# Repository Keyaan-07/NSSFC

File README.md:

# NSSFC

NSSFC is an FPV flight controller made with the STM32F405 and it has an IMU, Barometric pressure sensor and a magnetometer. It uses the betaflight as firmware(thus no firmware directory in this repository). The package is a typical 37mmx37mm.  

View the board on [KiCanvas](https://kicanvas.org/?repo=https%3A%2F%2Fgithub.com%2FKeyaan-07%2FNSSFC%2Ftree%2Fmain%2Fhardware)  

We made it to learn more about Flight controllers and make PCBs in a small area, especially something like 37x37mm!  

<!--  -->

## How to assemble:  
1. Order PCBs and components from the [/hardware/production](/hardware/production/) folder and order them from your supplier and PCB fab. Don't forget to get a stencil along with your PCB!
2. Place the PCB on a flat surface and place the stencil over it. 
3. Use medium-temp solder paste to put the soldermask pattern over the PCB. 
4. Carefully place all the components, use the [ibom](/hardware/bom/ibom.html) for smooth placement. 
5. Solder it in a reflow-oven or a hotplate!
6. You're done!!

## Firmware Flashing Guide:  
1. Hold the BOOT0 button and put in the USB into your computer.  
2. We will use [betaflight web configurator](https://app.betaflight.com/) to flash the lastest build. [here](https://github.com/betaflight/betaflight/releases/download/2026.6.2/betaflight_2026.6.2_STM32F405.hex) is the latest build, download it!  
3. Also, download the config file from the [/config](/config/) folder. 
3. Go to the firmware flasher tab in the betaflight app.  
4. Click load local firmware, then select the downloaded `nssfc.config` file.  
5. Click Load local firmware again, and then select the `.hex` file you downloaded.  
6. Click Flash firmware to flash the firmware.  
7. After the firmware has been flashed, go to the home page and then click connect, to connect to the FC.  
8. A prompt asking _Apply custom defaults_ should pop up, click yes. 
9. Your flashing part is done! Happy Flying!

[here](https://betaflight.com/docs/wiki/guides/archive/Unified-Targets) is the source for the above steps. 

# BOM
|Designator                                                |Function        |Value           |Footprint                               |Quantity|Price        |Amount |Link                                              |
|----------------------------------------------------------|----------------|----------------|----------------------------------------|--------|-------------|-------|--------------------------------------------------|
|PCB                                                       |                |                |                                        |5       |             |2      |https://jlcpcb.com/                               |
|Stencil                                                   |                |                |                                        |1       |             |3.1    |https://jlcpcb.com/                               |
|C1, C16, C2                                               |Capacitor       |2.2u            |402                                     |3       |0.0054       |0.0162 |https://www.lcsc.com/product-detail/C12530.html   |
|C10                                                       |Capacitor       |1u              |402                                     |1       |0.047        |0.047  |https://www.lcsc.com/product-detail/C1518208.html |
|C11                                                       |Capacitor       |4.7u            |402                                     |1       |0.0275       |0.0275 |https://www.lcsc.com/product-detail/C20624278.html|
|C12, C13, C14, C15, C17, C19, C23, C25, C5, C6, C7, C8, C9|Capacitor       |100n            |402                                     |13      |0.0045       |0.0585 |https://www.lcsc.com/product-detail/C5182432.html |
|C20                                                       |Capacitor       |22u             |805                                     |1       |0.17         |0.17   |https://www.lcsc.com/product-detail/C602037.html  |
|C21, C22, C24                                             |Capacitor       |10u             |805                                     |3       |0.18         |0.54   |https://www.lcsc.com/product-detail/C2932476.html |
|C3, C4                                                    |Capacitor       |15p             |402                                     |2       |0.025        |0.05   |https://www.lcsc.com/product-detail/C441742.html  |
|D1, D2                                                    |Diode           |D_Schottky      |D_SOD-123F                              |2       |0.035        |0.07   |https://www.lcsc.com/product-detail/C432153.html  |
|D3, D4, D5                                                |LED             |LED             |402                                     |3       |0.054        |0.162  |https://www.lcsc.com/product-detail/C2980183.html |
|J1                                                        |USB C receptacle|USB_C_Receptacle|USB_C_Receptacle_XKB_U262-16XN-4BVC11   |1       |0.059        |0.059  |https://www.lcsc.com/product-detail/C393939.html  |
|L1                                                        |Inductor        |4.7u            |L_Changjiang_FNR4020S                   |1       |0.082        |0.082  |https://www.lcsc.com/product-detail/C167828.html  |
|R1, R6                                                    |Resistor        |10k             |402                                     |2       |0.0425       |0.085  |https://www.lcsc.com/product-detail/C3020235.html |
|R2, R3                                                    |Resistor        |4.7k            |402                                     |2       |0.0026       |0.0052 |https://www.lcsc.com/product-detail/C25900.html   |
|R4, R5                                                    |Resistor        |5.1k            |402                                     |2       |0.006        |0.012  |https://www.lcsc.com/product-detail/C278598.html  |
|R7                                                        |Resistor        |1k              |402                                     |1       |0.066        |0.066  |https://www.lcsc.com/product-detail/C427241.html  |
|R8                                                        |Resistor        |220             |402                                     |1       |0.002        |0.002  |https://www.lcsc.com/product-detail/C2909336.html |
|R9                                                        |Resistor        |100             |402                                     |1       |0.026        |0.026  |https://www.lcsc.com/product-detail/C427204.html  |
|SW1                                                       |Push button     |SW_Push         |SW_SPST_PTS810                          |1       |0.3425       |0.3425 |https://www.lcsc.com/product-detail/C221895.html  |
|U1                                                        |MCU             |STM32F405RGTx   |LQFP-64_10x10mm_P0.5mm                  |1       |6.01         |6.01   |https://www.lcsc.com/product-detail/C15742.html   |
|U2                                                        |Flash           |W25Q128JVP      |WSON-8-1EP_6x5mm_P1.27mm_EP3.4x4.3mm    |1       |2.82         |2.82   |https://www.lcsc.com/product-detail/C2441427.html |
|U3                                                        |magnetometer    |QMC5883P        |LGA-16_3x3_Pitch0.5mm_QMC5883P          |1       |1.57         |1.57   |https://www.lcsc.com/product-detail/C2847467.html |
|U4                                                        |IMU             |ICM-20602       |LGA-16_3x3mm_P0.5mm_LayoutBorder3x5y    |1       |6.02         |6.02   |https://www.lcsc.com/product-detail/C97633.html   |
|U5                                                        |Pressure Sensor |BMP580          |ST_HLGA-10_2x2mm_P0.5mm_LayoutBorder3x2y|1       |1.21         |1.21   |https://www.lcsc.com/product-detail/C22391138.html|
|U6                                                        |Buck            |AP63205WU       |TSOT-23-6                               |1       |0.43         |0.43   |https://www.lcsc.com/product-detail/C2071056.html |
|U7                                                        |LDO             |TLV75733PDBV    |SOT-23-5                                |1       |0.2          |0.2    |https://www.lcsc.com/product-detail/C485517.html  |
|Y1                                                        |Crystals        |25MHz           |Crystal_SMD_3225-4Pin_3.2x2.5mm         |1       |0.1          |0.1    |https://www.lcsc.com/product-detail/C70582.html   |
|                                                          |                |                |                                        |        |LCSC shipping|9.3    |                                                  |
|                                                          |                |                |                                        |        |PCB Shipping |11.25  |                                                  |
|                                                          |                |                |                                        |        |Total        |45.8309|                                                  |

Made by Keyaan and Ahad

# Licensing
Licensed under the MIT License!

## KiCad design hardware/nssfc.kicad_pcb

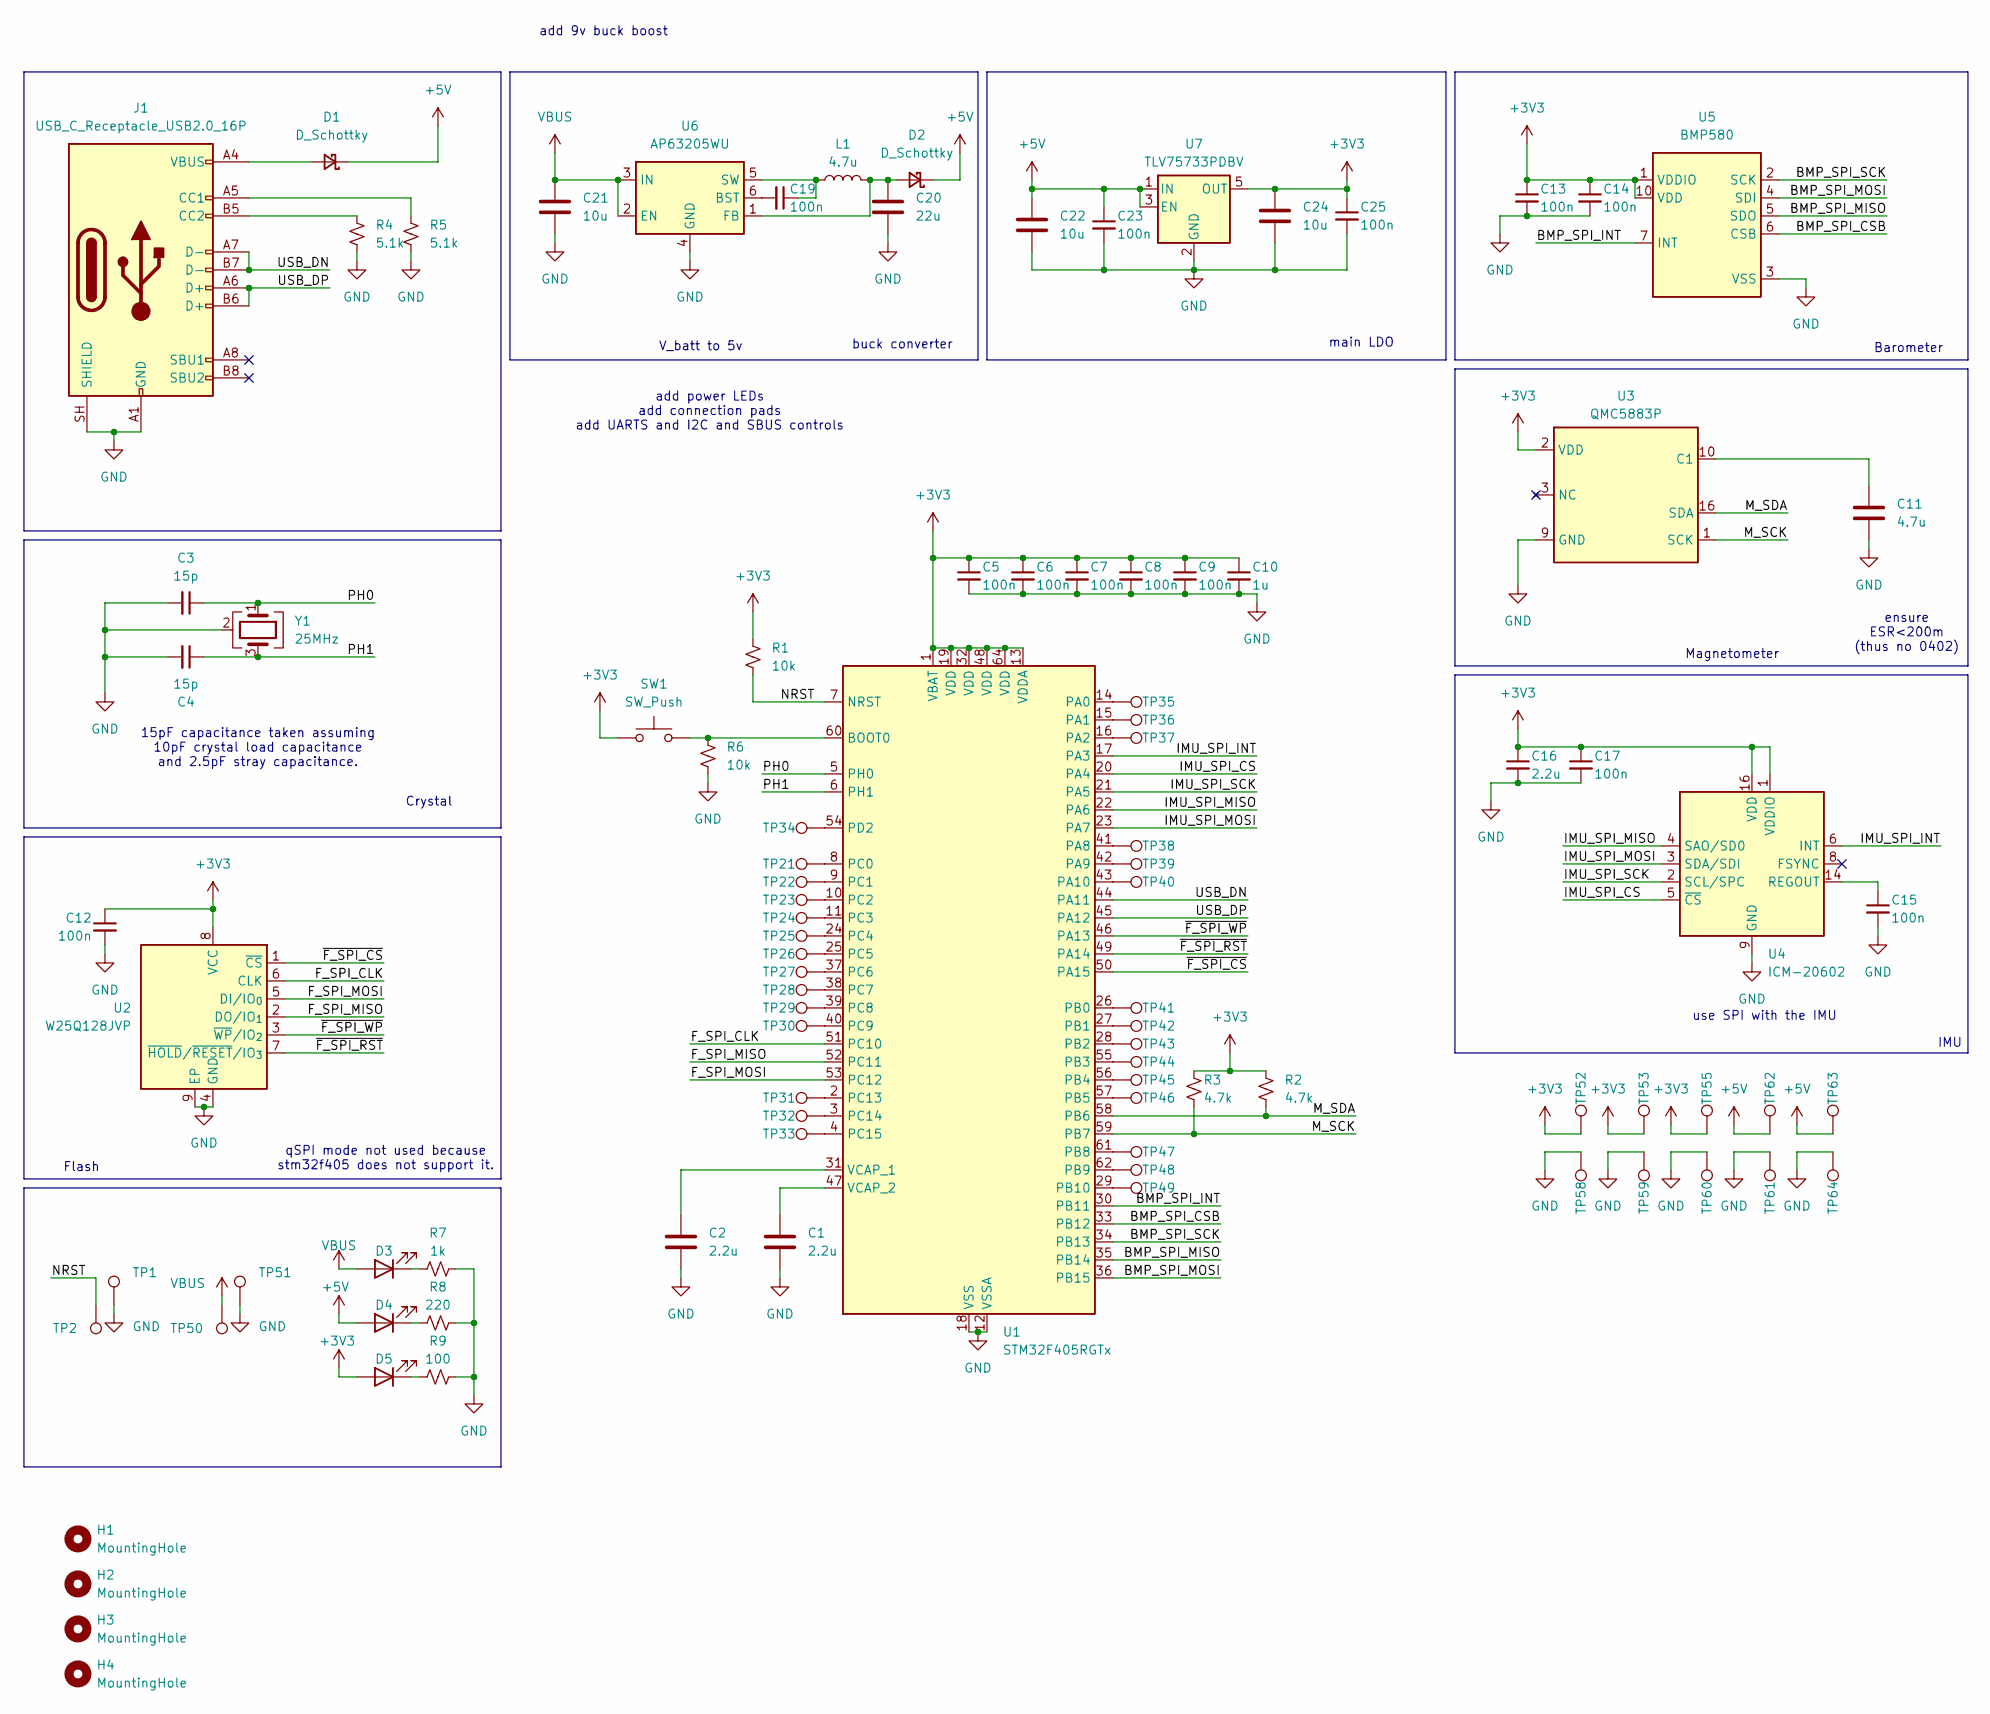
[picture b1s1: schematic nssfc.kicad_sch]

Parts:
C1, C2, C16: 2.2u; C_0402_1005Metric
C3, C4: 15p; C_0402_1005Metric
C5, C6, C7, C8, C9, C12, C13, C14, C15, C17, C19, C23, C25: 100n; C_0402_1005Metric
C10: 1u; C_0402_1005Metric
C11: 4.7u; C_0805_2012Metric
C20: 22u; C_0805_2012Metric
C21, C22, C24: 10u; C_0805_2012Metric
D1, D2: D_Schottky; D_SOD-123F
D3, D4, D5: LED; LED_0402_1005Metric
H1, H2, H3, H4: MountingHole; MountingHole_3.2mm_M3
J1: USB_C_Receptacle_USB2.0_16P; USB_C_Receptacle_XKB_U262-16XN-4BVC11
L1: 4.7u; L_Changjiang_FNR4020S
R1, R6: 10k; R_0402_1005Metric
R2, R3: 4.7k; R_0402_1005Metric
R4, R5: 5.1k; R_0402_1005Metric
R7: 1k; R_0402_1005Metric
R8: 220; R_0402_1005Metric
R9: 100; R_0402_1005Metric
SW1: SW_Push; SW_SPST_PTS810
TP1, TP2: TestPoint; TestPoint_Pad_1.0x1.0mm
TP21, TP22, TP23, TP24, TP25, TP26, TP27, TP28, TP29, TP30, TP31, TP32, TP33, TP34, TP35, TP36, TP37, TP38, TP39, TP40, TP41, TP42, TP43, TP44, TP45, TP46, TP47, TP48, TP49, TP52, TP53, TP55, TP58, TP59, TP60, TP61, TP62, TP63, TP64: TestPoint; PAD_1.5mm
TP50, TP51: TestPoint; TestPoint_Pad_2.0x2.0mm
U1: STM32F405RGTx; LQFP-64_10x10mm_P0.5mm
U2: W25Q128JVP; WSON-8-1EP_6x5mm_P1.27mm_EP3.4x4.3mm
U3: QMC5883P; LGA-16_3x3_Pitch0.5mm_QMC5883P
U4: ICM-20602; LGA-16_3x3mm_P0.5mm_LayoutBorder3x5y
U5: BMP580; ST_HLGA-10_2x2mm_P0.5mm_LayoutBorder3x2y
U6: AP63205WU; TSOT-23-6
U7: TLV75733PDBV; SOT-23-5
Y1: 25MHz; Crystal_SMD_3225-4Pin_3.2x2.5mm

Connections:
+3V3: C5.1, C6.1, C7.1, C8.1, C9.1, C10.1, C12.1, C13.1, C14.1, C16.1, C17.1, C24.1, C25.1, D5.2 (A), R1.1, R2.1, R3.1, SW1.1, TP52.1 (1_1), TP53.1 (1_1), TP55.1 (1_1), U1.1 (VBAT), U1.13 (VDDA), U1.19 (VDD), U1.32 (VDD), U1.48 (VDD), U1.64 (VDD), U2.8 (VCC), U3.2 (VDD), U4.1 (VDDIO), U4.16 (VDD), U5.1 (VDDIO), U5.10 (VDD), U7.5 (OUT)
+5V: C22.1, C23.1, D1.1 (K), D2.1 (K), D4.2 (A), TP62.1 (1_1), TP63.1 (1_1), U7.1 (IN), U7.3 (EN)
/BMP_SPI_CSB: U1.33 (PB12), U5.6 (CSB)
/BMP_SPI_INT: U1.30 (PB11), U5.7 (INT)
/BMP_SPI_MISO: U1.35 (PB14), U5.5 (SDO)
/BMP_SPI_MOSI: U1.36 (PB15), U5.4 (SDI)
/BMP_SPI_SCK: U1.34 (PB13), U5.2 (SCK)
/F_SPI_CLK: U1.51 (PC10), U2.6 (CLK)
/F_SPI_MISO: U1.52 (PC11), U2.2 (DO/IO_{1})
/F_SPI_MOSI: U1.53 (PC12), U2.5 (DI/IO_{0})
/IMU_SPI_CS: U1.20 (PA4), U4.5 (~CS)
/IMU_SPI_INT: U1.17 (PA3), U4.6 (INT)
/IMU_SPI_MISO: U1.22 (PA6), U4.4 (SAO/SD0)
/IMU_SPI_MOSI: U1.23 (PA7), U4.3 (SDA/SDI)
/IMU_SPI_SCK: U1.21 (PA5), U4.2 (SCL/SPC)
/M_SCK: R3.2, U1.59 (PB7), U3.1 (SCK)
/M_SDA: R2.2, U1.58 (PB6), U3.16 (SDA)
/NRST: R1.2, TP2.1 (1_1), U1.7 (NRST)
/PH0: C3.1, U1.5 (PH0), Y1.1
/PH1: C4.1, U1.6 (PH1), Y1.3
/USB_DN: J1.A7 (D-), J1.B7 (D-), U1.44 (PA11)
/USB_DP: J1.A6 (D+), J1.B6 (D+), U1.45 (PA12)
/~F_SPI_CS: U1.50 (PA15), U2.1 (~CS)
/~F_SPI_RST: U1.49 (PA14), U2.7 (~HOLD/~RESET/IO_{3})
/~F_SPI_WP: U1.46 (PA13), U2.3 (~WP/IO_{2})
GND: C1.2, C2.2, C3.2, C4.2, C5.2, C6.2, C7.2, C8.2, C9.2, C10.2, C11.2, C12.2, C13.2, C14.2, C15.2, C16.2, C17.2, C20.2, C21.2, C22.2, C23.2, C24.2, C25.2, J1.A1 (GND), J1.A12 (GND), J1.B1 (GND), J1.B12 (GND), J1.SH (SHIELD), R4.2, R5.2, R6.2, R7.2, R8.2, R9.2, TP1.1 (1_1), TP51.1 (1_1), TP58.1 (1_1), TP59.1 (1_1), TP60.1 (1_1), TP61.1 (1_1), TP64.1 (1_1), U1.12 (VSSA), U1.18 (VSS), U1.63 (VSS), U2.4 (GND), U2.9 (EP), U3.9 (GND), U3.11 (GND), U4.9 (GND), U4.10 (GND), U4.11 (GND), U4.12 (GND), U4.13 (GND), U4.15 (GND), U5.3 (VSS), U5.8 (VSS), U5.9 (VSS), U6.4 (GND), U7.2 (GND), Y1.2 (G), Y1.4 (G)
unnamed: D1.2 (A), J1.A4 (VBUS), J1.A9 (VBUS), J1.B4 (VBUS), J1.B9 (VBUS)
unnamed: C20.1, D2.2 (A), L1.2, U6.1 (FB)
unnamed: D3.1 (K), R7.1
unnamed: D4.1 (K), R8.1
unnamed: D5.1 (K), R9.1
unnamed: J1.A5 (CC1), R5.1
unnamed: J1.B5 (CC2), R4.1
unnamed: R6.1, SW1.2, U1.60 (BOOT0)
unnamed: TP35.1 (1_1), U1.14 (PA0)
unnamed: TP36.1 (1_1), U1.15 (PA1)
unnamed: TP37.1 (1_1), U1.16 (PA2)
unnamed: TP38.1 (1_1), U1.41 (PA8)
unnamed: TP39.1 (1_1), U1.42 (PA9)
unnamed: TP40.1 (1_1), U1.43 (PA10)
unnamed: TP41.1 (1_1), U1.26 (PB0)
unnamed: TP42.1 (1_1), U1.27 (PB1)
unnamed: TP43.1 (1_1), U1.28 (PB2)
unnamed: TP44.1 (1_1), U1.55 (PB3)
unnamed: TP45.1 (1_1), U1.56 (PB4)
unnamed: TP46.1 (1_1), U1.57 (PB5)
unnamed: TP47.1 (1_1), U1.61 (PB8)
unnamed: TP48.1 (1_1), U1.62 (PB9)
unnamed: TP49.1 (1_1), U1.29 (PB10)
unnamed: TP21.1 (1_1), U1.8 (PC0)
unnamed: TP22.1 (1_1), U1.9 (PC1)
unnamed: TP23.1 (1_1), U1.10 (PC2)
unnamed: TP24.1 (1_1), U1.11 (PC3)
unnamed: TP25.1 (1_1), U1.24 (PC4)
unnamed: TP26.1 (1_1), U1.25 (PC5)
unnamed: TP27.1 (1_1), U1.37 (PC6)
unnamed: TP28.1 (1_1), U1.38 (PC7)
unnamed: TP29.1 (1_1), U1.39 (PC8)
unnamed: TP30.1 (1_1), U1.40 (PC9)
unnamed: TP31.1 (1_1), U1.2 (PC13)
unnamed: TP32.1 (1_1), U1.3 (PC14)
unnamed: TP33.1 (1_1), U1.4 (PC15)
unnamed: TP34.1 (1_1), U1.54 (PD2)
unnamed: C2.1, U1.31 (VCAP_1)
unnamed: C1.1, U1.47 (VCAP_2)
unnamed: C11.1, U3.10 (C1)
unnamed: C15.1, U4.14 (REGOUT)
unnamed: C19.2, U6.6 (BST)
unnamed: C19.1, L1.1, U6.5 (SW)
VBUS: C21.1, D3.2 (A), TP50.1 (1_1), U6.2 (EN), U6.3 (IN)

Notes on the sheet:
add power LEDs add connection pads add UARTS and I2C and SBUS controls
main LDO
Flash
qSPI mode not used because stm32f405 does not support it.
15pF capacitance taken assuming 10pF crystal load capacitance and 2.5pF stray capacitance.
add 9v buck boost
ensure ESR<200m (thus no 0402)
IMU
Crystal
V_batt to 5v
buck converter
Barometer
Magnetometer
use SPI with the IMU

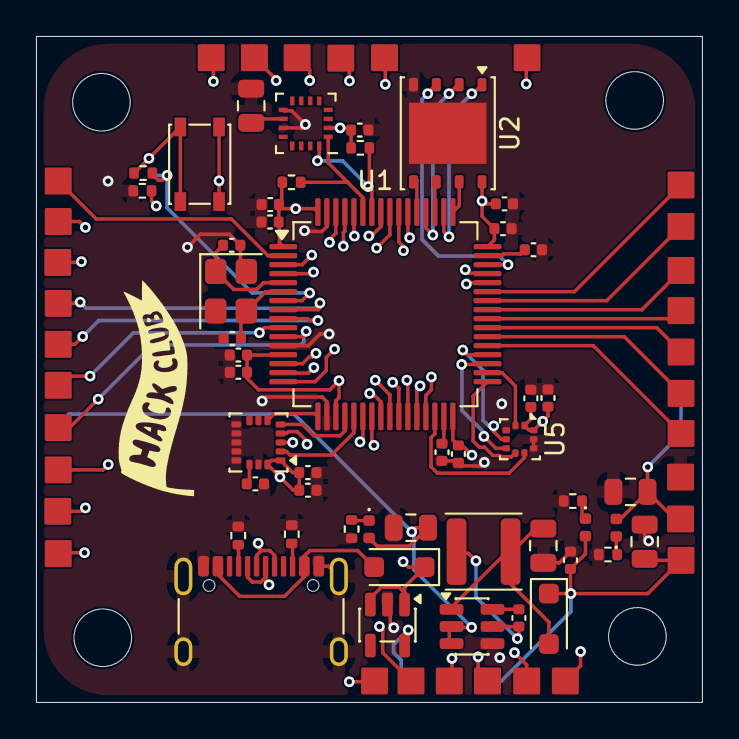
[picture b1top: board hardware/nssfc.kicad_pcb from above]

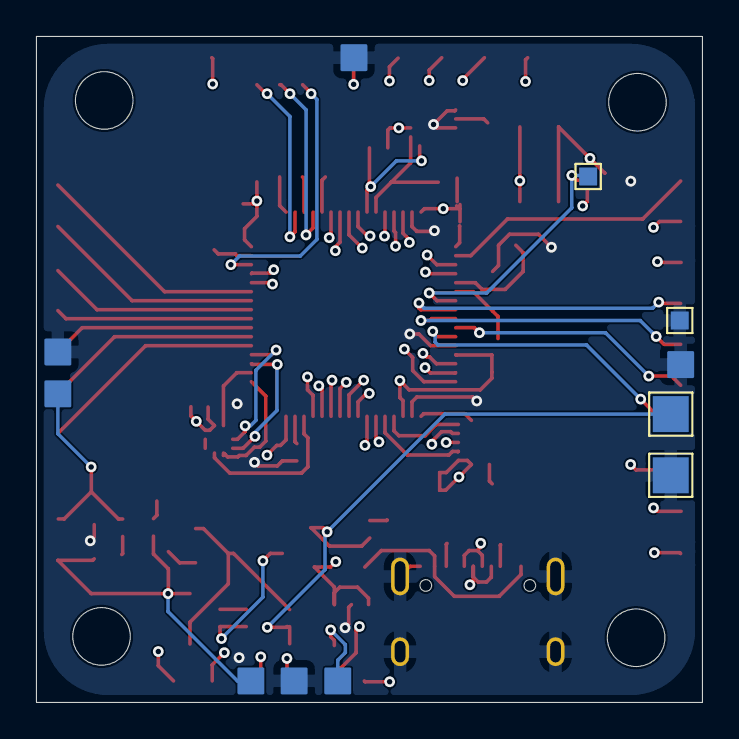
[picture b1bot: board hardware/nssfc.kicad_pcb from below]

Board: 4 copper layers, 37.0 x 37.0 mm, 96 parts (11 on the bottom side), 70 nets.

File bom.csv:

Designator,Function,Value,Footprint,Quantity,Price,Amount,Link
PCB,,,,5,,2,https://jlcpcb.com/
Stencil,,,,1,,3.1,https://jlcpcb.com/
"C1, C16, C2",Capacitor,2.2u,402,3,0.0054,0.0162,https://www.lcsc.com/product-detail/C12530.html
C10,Capacitor,1u,402,1,0.047,0.047,https://www.lcsc.com/product-detail/C1518208.html
C11,Capacitor,4.7u,402,1,0.0275,0.0275,https://www.lcsc.com/product-detail/C20624278.html
"C12, C13, C14, C15, C17, C19, C23, C25, C5, C6, C7, C8, C9",Capacitor,100n,402,13,0.0045,0.0585,https://www.lcsc.com/product-detail/C5182432.html
C20,Capacitor,22u,805,1,0.17,0.17,https://www.lcsc.com/product-detail/C602037.html
"C21, C22, C24",Capacitor,10u,805,3,0.18,0.54,https://www.lcsc.com/product-detail/C2932476.html
"C3, C4",Capacitor,15p,402,2,0.025,0.05,https://www.lcsc.com/product-detail/C441742.html
"D1, D2",Diode,D_Schottky,D_SOD-123F,2,0.035,0.07,https://www.lcsc.com/product-detail/C432153.html
"D3, D4, D5",LED,LED,402,3,0.054,0.162,https://www.lcsc.com/product-detail/C2980183.html
J1,USB C receptacle,USB_C_Receptacle,USB_C_Receptacle_XKB_U262-16XN-4BVC11,1,0.059,0.059,https://www.lcsc.com/product-detail/C393939.html
L1,Inductor,4.7u,L_Changjiang_FNR4020S,1,0.082,0.082,https://www.lcsc.com/product-detail/C167828.html
"R1, R6",Resistor,10k,402,2,0.0425,0.085,https://www.lcsc.com/product-detail/C3020235.html
"R2, R3",Resistor,4.7k,402,2,0.0026,0.0052,https://www.lcsc.com/product-detail/C25900.html
"R4, R5",Resistor,5.1k,402,2,0.006,0.012,https://www.lcsc.com/product-detail/C278598.html
R7,Resistor,1k,402,1,0.066,0.066,https://www.lcsc.com/product-detail/C427241.html
R8,Resistor,220,402,1,0.002,0.002,https://www.lcsc.com/product-detail/C2909336.html
R9,Resistor,100,402,1,0.026,0.026,https://www.lcsc.com/product-detail/C427204.html
SW1,Push button,SW_Push,SW_SPST_PTS810,1,0.3425,0.3425,https://www.lcsc.com/product-detail/C221895.html
U1,MCU,STM32F405RGTx,LQFP-64_10x10mm_P0.5mm,1,6.01,6.01,https://www.lcsc.com/product-detail/C15742.html
U2,Flash,W25Q128JVP,WSON-8-1EP_6x5mm_P1.27mm_EP3.4x4.3mm,1,2.82,2.82,https://www.lcsc.com/product-detail/C2441427.html
U3,magnetometer,QMC5883P,LGA-16_3x3_Pitch0.5mm_QMC5883P,1,1.57,1.57,https://www.lcsc.com/product-detail/C2847467.html
U4,IMU,ICM-20602,LGA-16_3x3mm_P0.5mm_LayoutBorder3x5y,1,6.02,6.02,https://www.lcsc.com/product-detail/C97633.html
U5,Pressure Sensor,BMP580,ST_HLGA-10_2x2mm_P0.5mm_LayoutBorder3x2y,1,1.21,1.21,https://www.lcsc.com/product-detail/C22391138.html
U6,Buck,AP63205WU,TSOT-23-6,1,0.43,0.43,https://www.lcsc.com/product-detail/C2071056.html
U7,LDO,TLV75733PDBV,SOT-23-5,1,0.2,0.2,https://www.lcsc.com/product-detail/C485517.html
Y1,Crystals,25MHz,Crystal_SMD_3225-4Pin_3.2x2.5mm,1,0.1,0.1,https://www.lcsc.com/product-detail/C70582.html
,,,,,LCSC shipping,9.3,
,,,,,PCB Shipping,11.25,
,,,,,Total,45.8309,

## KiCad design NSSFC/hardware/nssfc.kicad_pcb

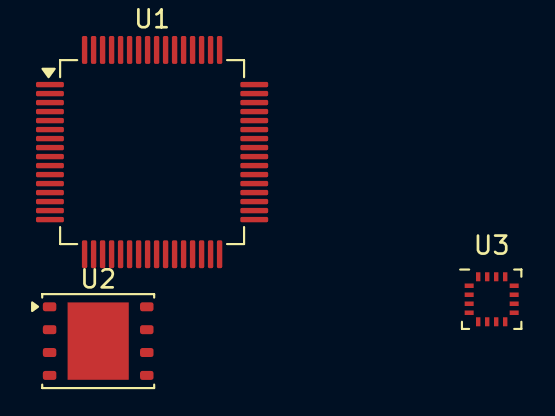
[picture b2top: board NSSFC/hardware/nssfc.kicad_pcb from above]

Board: 2 copper layers, 3 parts (0 on the bottom side), 3 nets, no tracks yet.

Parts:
U1: STM32F405RGTx; LQFP-64_10x10mm_P0.5mm
U2: W25Q128JVP; WSON-8-1EP_6x5mm_P1.27mm_EP3.4x4.3mm
U3: QMC5883P; LGA-16_3x3_Pitch0.5mm_QMC5883P

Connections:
+3V3: U1.1 (VBAT), U1.13 (VDDA), U1.19 (VDD), U1.32 (VDD), U1.48 (VDD), U1.64 (VDD), U2.8 (VCC)
GND: U1.12 (VSSA), U1.18 (VSS), U1.63 (VSS), U2.4 (GND), U2.9 (EP)
unnamed: U3.9 (GND), U3.11 (GND)
